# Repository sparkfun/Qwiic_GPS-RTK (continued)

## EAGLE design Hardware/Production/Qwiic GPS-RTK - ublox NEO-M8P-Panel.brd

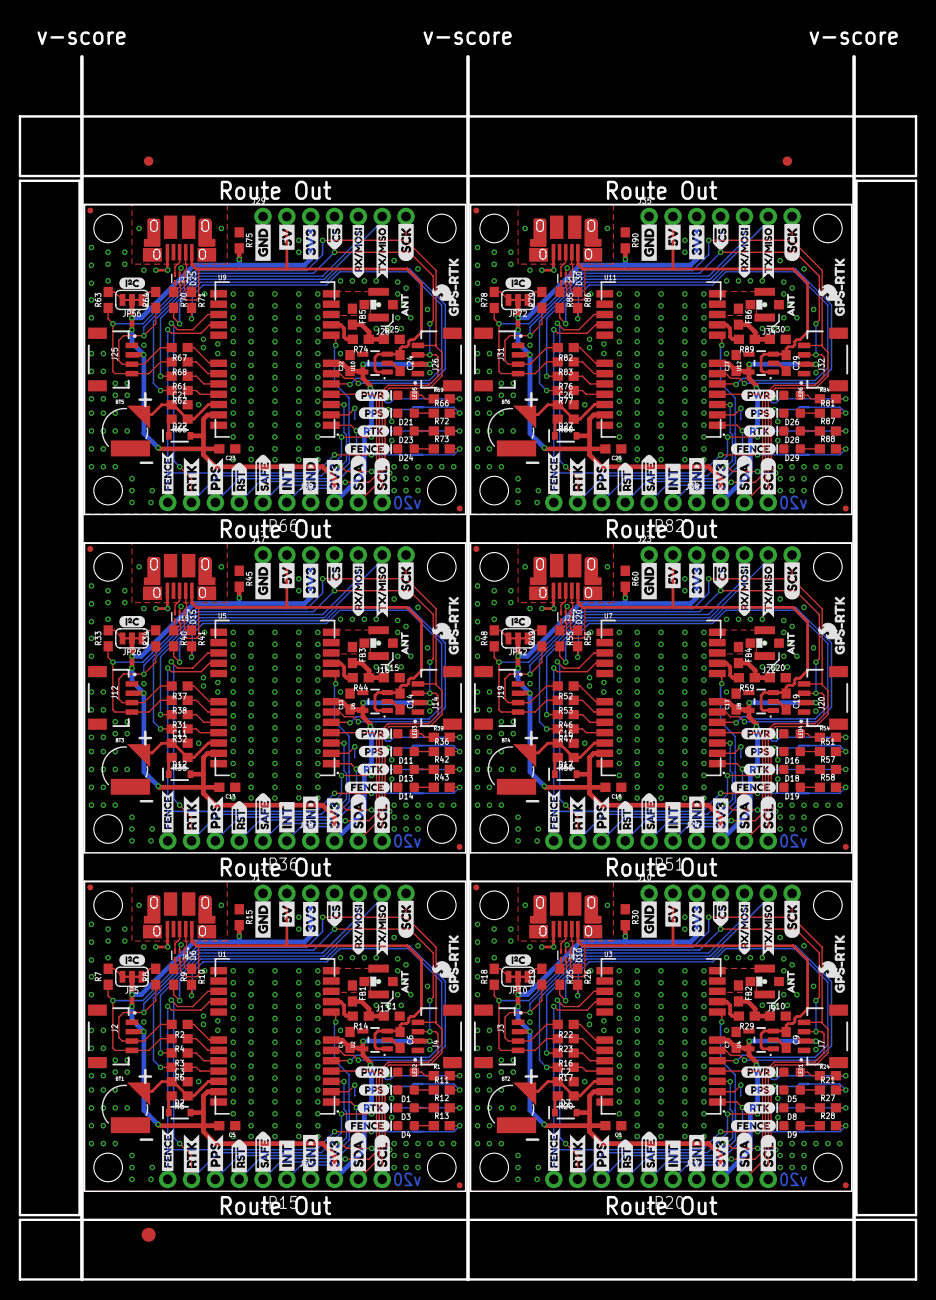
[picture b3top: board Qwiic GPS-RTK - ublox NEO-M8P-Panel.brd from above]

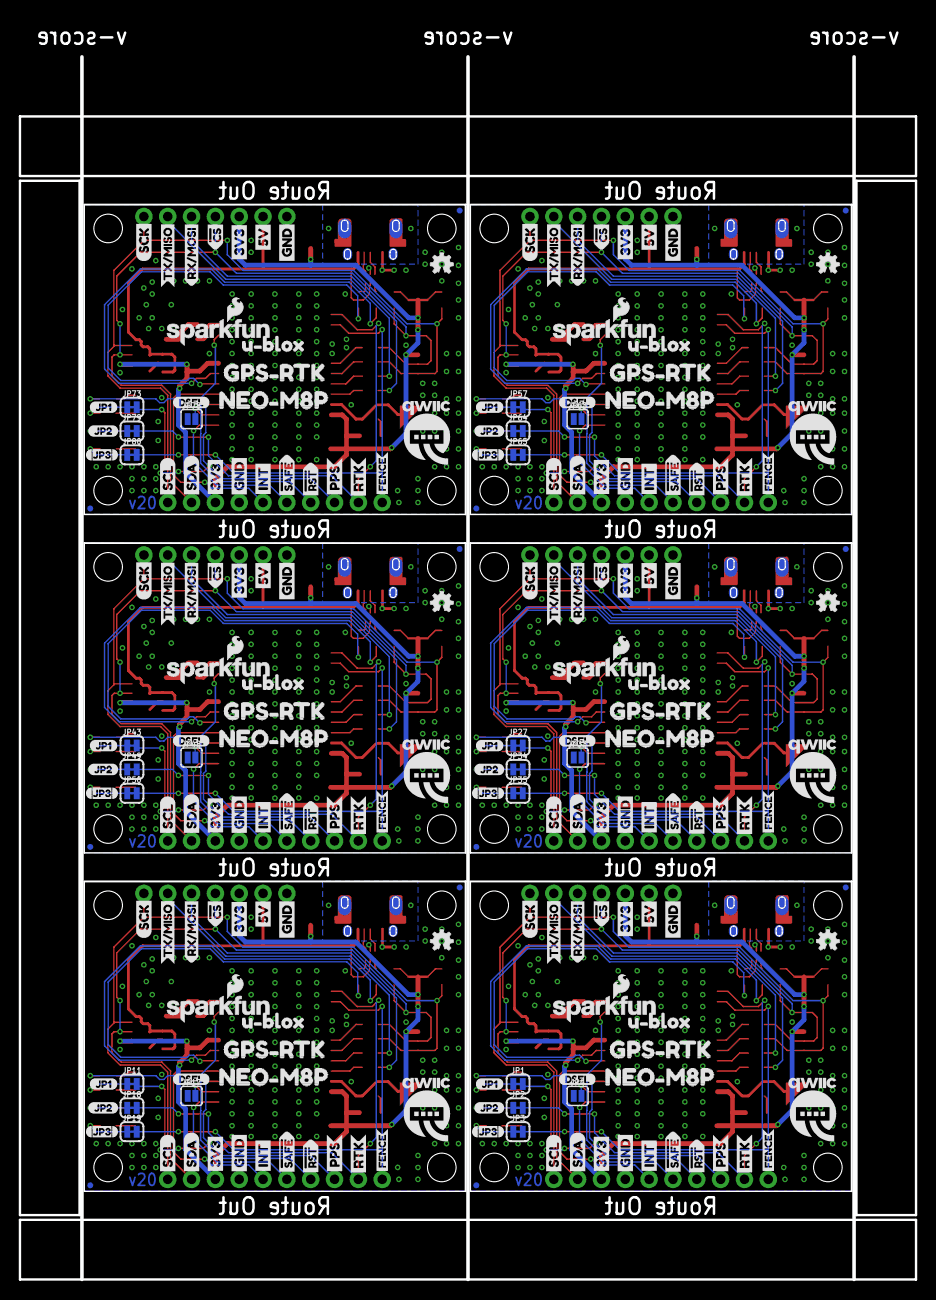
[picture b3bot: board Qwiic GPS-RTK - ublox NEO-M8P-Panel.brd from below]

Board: 2 copper layers, 95.5 x 130.3 mm, 615 parts (198 on the bottom side), 234 nets.

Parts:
BT1, BT2, BT3, BT4, BT5, BT6: ML414H_IV01E_BATTERY; ML414H_IV01E
C1, C10, C15, C20, C25, C30: 47pF; 0603
C2, C3, C4, C6, C7, C9, C11, C12, C14, C16, C17, C19, C21, C22, C24, C26, C27, C29: 1.0uF; 0603
C5, C8, C13, C18, C23, C28: 0.1uF; 0603
D1, D5, D11, D16, D21, D26: Yellow; LED-0603
D2, D7, D12, D17, D22, D27: 0.5A/40V/420mV; SOD-323
D3, D8, D13, D18, D23, D28: GREEN; LED-0603
D4, D9, D14, D19, D24, D29: BLUE; LED-0603
D6, D10, D15, D20, D25, D30: PRTR5V0U2F; SOT886
E$1, E$2: FIDUCIAL-1X2
E$3: FIDUCIAL-1.5X3
FB1, FB2, FB3, FB4, FB5, FB6: 30Ω/1.8A; 0603
J1, J10, J17, J23, J29, J35: 1X07_NO_SILK
J2, J3, J4, J7, J12, J14, J19, J20, J25, J26, J31, J32: Qwiic Right Angle; JST04_1MM_RA
J5, J11, J18, J24, J30, J36: 1X04_NO_SILK
J6, J8, J15, J21, J27, J33: USB-MICROB-PTH-MILL
J9, J13, J16, J22, J28, J34: U.FL
JP1, JP2, JP3, JP11, JP18, JP19, JP27, JP34, JP35, JP43, JP49, JP50, JP57, JP64, JP65, JP73, JP79, JP80: JUMPER-SMT_2_NC_TRACE_SILK; SMT-JUMPER_2_NC_TRACE_SILK
JP4, JP17, JP33, JP48, JP63, JP78: JUMPER-SMT_2_NO_SILK; SMT-JUMPER_2_NO_SILK
JP5, JP10, JP26, JP42, JP56, JP72: JUMPER-SMT_3_2-NC_TRACE_SILK; SMT-JUMPER_3_2-NC_TRACE_SILK
JP6, JP7, JP14, JP16, JP22, JP23, JP30, JP31, JP32, JP37, JP38, JP41, JP46, JP47, JP52, JP53, JP60, JP62, JP67, JP68, JP76, JP77, JP91, JP101: STAND-OFFTIGHT; STAND-OFF-TIGHT
JP8, JP9, JP12, JP13, JP21, JP24, JP25, JP28, JP29, JP39, JP40, JP44, JP45, JP54, JP55, JP58, JP59, JP61, JP69, JP70, JP71, JP74, JP75, JP81: FIDUCIALUFIDUCIAL; FIDUCIAL-MICRO
JP15, JP20, JP36, JP51, JP66, JP82: 1X06_NO_SILK
LED1, LED2, LED3, LED4, LED5, LED6: RED; LED-0603
LOGO1, LOGO3, LOGO5, LOGO7, LOGO9, LOGO11: OSHW-LOGOMINI; OSHW-LOGO-MINI
LOGO2, LOGO4, LOGO6, LOGO8, LOGO10, LOGO12: SFE_LOGO_NAME_FLAME.1_INCH; SFE_LOGO_NAME_FLAME_.1
R1, R5, R11, R12, R13, R20, R21, R24, R27, R28, R35, R36, R39, R42, R43, R50, R51, R54, R57, R58, R65, R66, R69, R72, R73, R80, R81, R84, R87, R88: 1k; 0603
R2, R3, R4, R6, R16, R17, R22, R23, R31, R32, R37, R38, R46, R47, R52, R53, R61, R62, R67, R68, R76, R77, R82, R83: 33; 0603
R7, R8, R18, R19, R33, R34, R48, R49, R63, R64, R78, R79: 2.2k; 0603
R9, R10, R25, R26, R40, R41, R55, R56, R70, R71, R85, R86: 27; 0603
R14, R29, R44, R59, R74, R89: 10; 0603
R15, R30, R45, R60, R75, R90: 100k; 0603
U1, U3, U5, U7, U9, U11: NEO-M8P
U2, U4, U6, U8, U10, U12: 3.3V; SOT23-5
U$1, U$2, U$4, U$45, U$101, U$103, U$151, U$153, U$201, U$203, U$251, U$253: SDA-[)
U$3, U$5, U$42, U$46, U$102, U$104, U$152, U$154, U$202, U$204, U$252, U$254: SCL-[)
U$6, U$7, U$47, U$48, U$60, U$61, U$78, U$79, U$105, U$106, U$128, U$129, U$155, U$156, U$178, U$179, U$205, U$206, U$228, U$229, U$255, U$256, U$278, U$279: 3V3-04
U$8, U$9, U$49, U$50, U$62, U$63, U$80, U$81, U$107, U$108, U$130, U$131, U$157, U$158, U$180, U$181, U$207, U$208, U$230, U$231, U$257, U$258, U$280, U$281: GND-04
U$10, U$51, U$109, U$159, U$209, U$259: I_SUPER2_C-()-03
U$11, U$71, U$121, U$171, U$221, U$271: FENCE2
U$12, U$72, U$122, U$172, U$222, U$272: JP20
U$13, U$28, U$29, U$73, U$76, U$77, U$123, U$126, U$127, U$173, U$176, U$177, U$223, U$226, U$227, U$273, U$276, U$277: RTK1
U$14, U$17, U$74, U$75, U$124, U$125, U$174, U$175, U$224, U$225, U$274, U$275: FENCE0
U$15, U$16, U$56, U$57, U$110, U$111, U$160, U$161, U$210, U$211, U$260, U$261: INT8
U$18, U$89, U$139, U$189, U$239, U$289: PWR-()-03
U$19, U$20, U$90, U$91, U$140, U$141, U$190, U$191, U$240, U$241, U$290, U$291: 5V
U$21, U$82, U$132, U$182, U$232, U$282: GPS#RTK0
U$22, U$58, U$112, U$162, U$212, U$262: U#BLOX3
U$23, U$24, U$92, U$93, U$142, U$143, U$192, U$193, U$242, U$243, U$292, U$293: CS#-<]
U$25, U$83, U$133, U$183, U$233, U$283: JP10
U$26, U$97, U$147, U$197, U$247, U$297: RX#MOSI2
U$27, U$85, U$135, U$185, U$235, U$285: DSEL0
U$30, U$59, U$113, U$163, U$213, U$263: QWIIC-LOGO-MEDIUM
U$31, U$98, U$148, U$198, U$248, U$298: RX#MOSI3
U$32, U$84, U$134, U$184, U$234, U$284: JP32
U$33, U$96, U$146, U$196, U$246, U$296: SFE_LOGO_FLAME_.1
U$34, U$99, U$149, U$199, U$249, U$299: TX#MISO0
U$35, U$36, U$64, U$65, U$114, U$115, U$164, U$165, U$214, U$215, U$264, U$265: #RST3
U$37, U$100, U$150, U$200, U$250, U$300: TX#MISO1
U$38, U$41, U$94, U$95, U$144, U$145, U$194, U$195, U$244, U$245, U$294, U$295: SCK-(]-04
U$39, U$40, U$66, U$67, U$116, U$117, U$166, U$167, U$216, U$217, U$266, U$267: #SAFE1
U$43, U$44, U$68, U$69, U$118, U$119, U$168, U$169, U$218, U$219, U$268, U$269: PPS5
U$52, U$70, U$120, U$170, U$220, U$270: PPS0
U$53, U$86, U$136, U$186, U$236, U$286: NEO#M8P3
U$54, U$87, U$137, U$187, U$237, U$287: GPS#RTK1
U$55, U$88, U$138, U$188, U$238, U$288: ANT0

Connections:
3.3V: C4.1, C5.2, D2.A, J1.3, J2.2, J4.2, J5.2, JP5.2, R1.2, R15.2, U1.7, U1.23, U2.5
3.3V1: C7.1, C8.2, D7.A, J3.2, J7.2, J10.3, J11.2, JP10.2, R24.2, R30.2, U3.7, U3.23, U4.5
3.3V2: C12.1, C13.2, D12.A, J12.2, J14.2, J17.3, J18.2, JP26.2, R39.2, R45.2, U5.7, U5.23, U6.5
3.3V3: C17.1, C18.2, D17.A, J19.2, J20.2, J23.3, J24.2, JP42.2, R54.2, R60.2, U7.7, U7.23, U8.5
3.3V4: C22.1, C23.2, D22.A, J25.2, J26.2, J29.3, J30.2, JP56.2, R69.2, R75.2, U9.7, U9.23, U10.5
3.3V5: C27.1, C28.2, D27.A, J31.2, J32.2, J35.3, J36.2, JP72.2, R84.2, R90.2, U11.7, U11.23, U12.5
5V: C6.1, D6.5, J1.2, J6.VBUS, U2.1, U2.3
5V1: C9.1, D10.5, J8.VBUS, J10.2, U4.1, U4.3
5V2: C14.1, D15.5, J15.VBUS, J17.2, U6.1, U6.3
5V3: C19.1, D20.5, J21.VBUS, J23.2, U8.1, U8.3
5V4: C24.1, D25.5, J27.VBUS, J29.2, U10.1, U10.3
5V5: C29.1, D30.5, J33.VBUS, J35.2, U12.1, U12.3
!RESET: JP15.3, U1.8
!RESET1: JP20.3, U3.8
!RESET2: JP36.3, U5.8
!RESET3: JP51.3, U7.8
!RESET4: JP66.3, U9.8
!RESET5: JP82.3, U11.8
!SAFE: JP15.2, U1.1
!SAFE1: JP20.2, U3.1
!SAFE2: JP36.2, U5.1
!SAFE3: JP51.2, U7.1
!SAFE4: JP66.2, U9.1
!SAFE5: JP82.2, U11.1
ANT_VCC: C1.1, FB1.2, R14.1
ANT_VCC1: C10.1, FB2.2, R29.1
ANT_VCC2: C15.1, FB3.2, R44.1
ANT_VCC3: C20.1, FB4.2, R59.1
ANT_VCC4: C25.1, FB5.2, R74.1
ANT_VCC5: C30.1, FB6.2, R89.1
BACKUP: BT1.+, C3.1, R5.1, U1.22
BACKUP1: BT2.+, C2.1, R20.1, U3.22
BACKUP2: BT3.+, C11.1, R35.1, U5.22
BACKUP3: BT4.+, C16.1, R50.1, U7.22
BACKUP4: BT5.+, C21.1, R65.1, U9.22
BACKUP5: BT6.+, C26.1, R80.1, U11.22
D+: D6.4, R9.1
D+1: D10.4, R25.1
D+2: D15.4, R40.1
D+3: D20.4, R55.1
D+4: D25.4, R70.1
D+5: D30.4, R85.1
D-: D6.6, R10.1
D-1: D10.6, R26.1
D-2: D15.6, R41.1
D-3: D20.6, R56.1
D-4: D25.6, R71.1
D-5: D30.6, R86.1
D_SEL: JP4.2, U1.2
D_SEL1: JP17.2, U3.2
D_SEL2: JP33.2, U5.2
D_SEL3: JP48.2, U7.2
D_SEL4: JP63.2, U9.2
D_SEL5: JP78.2, U11.2
FENCE_STAT: JP3.2, JP15.6, U1.16
FENCE_STAT1: JP19.2, JP20.6, U3.16
FENCE_STAT2: JP35.2, JP36.6, U5.16
FENCE_STAT3: JP50.2, JP51.6, U7.16
FENCE_STAT4: JP65.2, JP66.6, U9.16
FENCE_STAT5: JP80.2, JP82.6, U11.16
GND: BT1.-, C1.2, C3.2, C4.2, C5.1, C6.2, D1.C, D3.C, D4.C, D6.2, J1.1, J2.1, J4.1, J5.1, J6.GND, J13.1, J13.2, JP4.1, LED2.C, R15.1, U1.10, U1.12, U1.13, U1.24, U2.2
GND1: BT2.-, C2.2, C7.2, C8.1, C9.2, C10.2, D5.C, D8.C, D9.C, D10.2, J3.1, J7.1, J8.GND, J9.1, J9.2, J10.1, J11.1, JP17.1, LED1.C, R30.1, U3.10, U3.12, U3.13, U3.24, U4.2
GND2: BT3.-, C11.2, C12.2, C13.1, C14.2, C15.2, D11.C, D13.C, D14.C, D15.2, J12.1, J14.1, J15.GND, J16.1, J16.2, J17.1, J18.1, JP33.1, LED3.C, R45.1, U5.10, U5.12, U5.13, U5.24, U6.2
GND3: BT4.-, C16.2, C17.2, C18.1, C19.2, C20.2, D16.C, D18.C, D19.C, D20.2, J19.1, J20.1, J21.GND, J22.1, J22.2, J23.1, J24.1, JP48.1, LED4.C, R60.1, U7.10, U7.12, U7.13, U7.24, U8.2
GND4: BT5.-, C21.2, C22.2, C23.1, C24.2, C25.2, D21.C, D23.C, D24.C, D25.2, J25.1, J26.1, J27.GND, J28.1, J28.2, J29.1, J30.1, JP63.1, LED5.C, R75.1, U9.10, U9.12, U9.13, U9.24, U10.2
GND5: BT6.-, C26.2, C27.2, C28.1, C29.2, C30.2, D26.C, D28.C, D29.C, D30.2, J31.1, J32.1, J33.GND, J34.1, J34.2, J35.1, J36.1, JP78.1, LED6.C, R90.1, U11.10, U11.12, U11.13, U11.24, U12.2
GPS_ANT1: FB1.1, J13.FEED, U1.11
GPS_ANT2: FB2.1, J9.FEED, U3.11
GPS_ANT3: FB3.1, J16.FEED, U5.11
GPS_ANT4: FB4.1, J22.FEED, U7.11
GPS_ANT5: FB5.1, J28.FEED, U9.11
GPS_ANT6: FB6.1, J34.FEED, U11.11
INT: JP15.1, U1.4
INT1: JP20.1, U3.4
INT2: JP36.1, U5.4
INT3: JP51.1, U7.4
INT4: JP66.1, U9.4
INT5: JP82.1, U11.4
unnamed: D3.A, R12.1
unnamed: D1.A, R11.1
unnamed: JP2.1, R12.2
unnamed: JP1.1, R11.2
unnamed: JP5.1, R8.2
unnamed: D2.C, R5.2
unnamed: D4.A, R13.1
unnamed: JP5.3, R7.2
unnamed: JP3.1, R13.2
unnamed: LED2.A, R1.1
unnamed: R9.2, U1.6
unnamed: R10.2, U1.5
unnamed: R14.2, U1.9
unnamed: JP10.1, R19.2
unnamed: JP10.3, R18.2
unnamed: D5.A, R21.1
unnamed: JP11.1, R21.2
unnamed: D7.C, R20.2
unnamed: LED1.A, R24.1
unnamed: R25.2, U3.6
unnamed: R26.2, U3.5
unnamed: D8.A, R27.1
unnamed: JP18.1, R27.2
unnamed: D9.A, R28.1
unnamed: JP19.1, R28.2
unnamed: R29.2, U3.9
unnamed: JP26.1, R34.2
unnamed: JP26.3, R33.2
unnamed: D11.A, R36.1
unnamed: JP27.1, R36.2
unnamed: D12.C, R35.2
unnamed: LED3.A, R39.1
unnamed: R40.2, U5.6
unnamed: R41.2, U5.5
unnamed: D13.A, R42.1
unnamed: JP34.1, R42.2
unnamed: D14.A, R43.1
unnamed: JP35.1, R43.2
unnamed: R44.2, U5.9
unnamed: JP42.1, R49.2
unnamed: JP42.3, R48.2
unnamed: D16.A, R51.1
unnamed: JP43.1, R51.2
unnamed: D17.C, R50.2
unnamed: LED4.A, R54.1
unnamed: R55.2, U7.6
unnamed: R56.2, U7.5
unnamed: D18.A, R57.1
unnamed: JP49.1, R57.2
unnamed: D19.A, R58.1
unnamed: JP50.1, R58.2
unnamed: R59.2, U7.9
unnamed: JP56.1, R64.2
unnamed: JP56.3, R63.2
unnamed: D21.A, R66.1
unnamed: JP57.1, R66.2
unnamed: D22.C, R65.2
unnamed: LED5.A, R69.1
unnamed: R70.2, U9.6
unnamed: R71.2, U9.5
unnamed: D23.A, R72.1
unnamed: JP64.1, R72.2
unnamed: D24.A, R73.1
unnamed: JP65.1, R73.2
unnamed: R74.2, U9.9
unnamed: JP72.1, R79.2
unnamed: JP72.3, R78.2
unnamed: D26.A, R81.1
unnamed: JP73.1, R81.2
unnamed: D27.C, R80.2
unnamed: LED6.A, R84.1
unnamed: R85.2, U11.6
unnamed: R86.2, U11.5
unnamed: D28.A, R87.1
unnamed: JP79.1, R87.2
unnamed: D29.A, R88.1
unnamed: JP80.1, R88.2
unnamed: R89.2, U11.9
PPS: JP1.2, JP15.4, U1.3
PPS1: JP11.2, JP20.4, U3.3
PPS2: JP27.2, JP36.4, U5.3
PPS3: JP43.2, JP51.4, U7.3
PPS4: JP57.2, JP66.4, U9.3
PPS5: JP73.2, JP82.4, U11.3
RTK_STAT: JP2.2, JP15.5, U1.15
RTK_STAT1: JP18.2, JP20.5, U3.15
RTK_STAT2: JP34.2, JP36.5, U5.15
RTK_STAT3: JP49.2, JP51.5, U7.15
RTK_STAT4: JP64.2, JP66.5, U9.15
RTK_STAT5: JP79.2, JP82.5, U11.15
RXI/MOSI: J1.5, R6.2
RXI/MOSI1: J10.5, R17.2
RXI/MOSI2: J17.5, R32.2
RXI/MOSI3: J23.5, R47.2
RXI/MOSI4: J29.5, R62.2
RXI/MOSI5: J35.5, R77.2
RXLV: R6.1, U1.21
RXLV1: R17.1, U3.21
RXLV2: R32.1, U5.21
RXLV3: R47.1, U7.21
RXLV4: R62.1, U9.21
RXLV5: R77.1, U11.21
SCL/SCK: J1.7, J2.4, J4.4, J5.4, R4.2, R7.1
SCL/SCK1: J3.4, J7.4, J10.7, J11.4, R18.1, R23.2
SCL/SCK2: J12.4, J14.4, J17.7, J18.4, R33.1, R38.2
SCL/SCK3: J19.4, J20.4, J23.7, J24.4, R48.1, R53.2
SCL/SCK4: J25.4, J26.4, J29.7, J30.4, R63.1, R68.2
SCL/SCK5: J31.4, J32.4, J35.7, J36.4, R78.1, R83.2
SCL_LV: R4.1, U1.19
SCL_LV1: R23.1, U3.19
SCL_LV2: R38.1, U5.19
SCL_LV3: R53.1, U7.19
SCL_LV4: R68.1, U9.19
SCL_LV5: R83.1, U11.19
SDA/!CS: J1.4, J2.3, J4.3, J5.3, R2.2, R8.1
SDA/!CS1: J3.3, J7.3, J10.4, J11.3, R19.1, R22.2
SDA/!CS2: J12.3, J14.3, J17.4, J18.3, R34.1, R37.2
SDA/!CS3: J19.3, J20.3, J23.4, J24.3, R49.1, R52.2
SDA/!CS4: J25.3, J26.3, J29.4, J30.3, R64.1, R67.2
SDA/!CS5: J31.3, J32.3, J35.4, J36.3, R79.1, R82.2
SDA_LV: R2.1, U1.18
SDA_LV1: R22.1, U3.18
SDA_LV2: R37.1, U5.18
SDA_LV3: R52.1, U7.18
SDA_LV4: R67.1, U9.18
SDA_LV5: R82.1, U11.18
SHLD: J6.SHIELD, J6.SHIELD2, J6.SHIELD3, J6.SHIELD4, J6.SHIELD5, J6.SHIELD6, J6.SHIELD7, J6.SHIELD8, J6.SHIELD9, J6.SHIELD10
SHLD1: J8.SHIELD, J8.SHIELD2, J8.SHIELD3, J8.SHIELD4, J8.SHIELD5, J8.SHIELD6, J8.SHIELD7, J8.SHIELD8, J8.SHIELD9, J8.SHIELD10
SHLD2: J15.SHIELD, J15.SHIELD2, J15.SHIELD3, J15.SHIELD4, J15.SHIELD5, J15.SHIELD6, J15.SHIELD7, J15.SHIELD8, J15.SHIELD9, J15.SHIELD10
SHLD3: J21.SHIELD, J21.SHIELD2, J21.SHIELD3, J21.SHIELD4, J21.SHIELD5, J21.SHIELD6, J21.SHIELD7, J21.SHIELD8, J21.SHIELD9, J21.SHIELD10
SHLD4: J27.SHIELD, J27.SHIELD2, J27.SHIELD3, J27.SHIELD4, J27.SHIELD5, J27.SHIELD6, J27.SHIELD7, J27.SHIELD8, J27.SHIELD9, J27.SHIELD10
SHLD5: J33.SHIELD, J33.SHIELD2, J33.SHIELD3, J33.SHIELD4, J33.SHIELD5, J33.SHIELD6, J33.SHIELD7, J33.SHIELD8, J33.SHIELD9, J33.SHIELD10
TXLV: R3.1, U1.20
TXLV1: R16.1, U3.20
TXLV2: R31.1, U5.20
TXLV3: R46.1, U7.20
TXLV4: R61.1, U9.20
TXLV5: R76.1, U11.20
TXO/MISO: J1.6, R3.2
TXO/MISO1: J10.6, R16.2
TXO/MISO2: J17.6, R31.2
TXO/MISO3: J23.6, R46.2
TXO/MISO4: J29.6, R61.2
TXO/MISO5: J35.6, R76.2
USB_D+: D6.3, J6.D+
USB_D+1: D10.3, J8.D+
USB_D+2: D15.3, J15.D+
USB_D+3: D20.3, J21.D+
USB_D+4: D25.3, J27.D+
USB_D+5: D30.3, J33.D+
USB_D-: D6.1, J6.D-
USB_D-1: D10.1, J8.D-
USB_D-2: D15.1, J15.D-
USB_D-3: D20.1, J21.D-
USB_D-4: D25.1, J27.D-
USB_D-5: D30.1, J33.D-

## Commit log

2018-09-11 Adding examples
2018-09-11 Removing eagle backup files
2018-09-14 Updating readme. Move examples to library.
2018-09-14 Fix schematic typo
2018-09-16 Modifications for reds.
2018-09-21 Panel update, now with route outs!
2018-10-17 Adding test jig
2018-11-01 Updating test jig to one button, add ground plane.
2020-01-10 Adds reflowable battery and moves all parts to use SparkFun Libraries
2020-01-10 Adds Panel for v20
2020-01-10 Renames zipped panel to v20
2020-01-13 Repanelizes for a larger panel 2x3 instead of 2x2
